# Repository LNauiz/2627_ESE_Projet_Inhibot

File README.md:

# 2627_ESE_Projet_Inhibot
_Projet réalisé par SERAPHIN Bradley, NAVIZET Léonard et BOISBOURDIN Lucas_

---
## Présentation du projet
Le but du projet est de créer un petit robot autonome capable de récupérer des canettes en fonction de leur couleur, par exemple rouge ou verte, et de déposer ces canettes dans une zone définis à l'avance.

Architecture du projet :

---

## Plan de la présentation
* [Conception du PCB](#conception-du-pcb)
* [Mécanique du robot](#mecanique-du-robot)
* [Code](#code)

---
## Conception du PCB
Pour la conception du PCB, plusieurs composants étaient recommandés :

- [Régulateur de tension 3.3V (BU)](https://github.com/LNauiz/2627_ESE_Projet_Inhibot/blob/main/Datasheet/Regulateur3-3V_buxxsd5wg-e.pdf)
- [Chargeur de batterie (BQ25896RTWR)](https://github.com/LNauiz/2627_ESE_Projet_Inhibot/blob/main/Datasheet/bq25896.pdf)
- [Jauge pour la batterie (BQ27220)](https://github.com/LNauiz/2627_ESE_Projet_Inhibot/blob/main/Datasheet/bq27220.pdf)
- [Driver de moteur (DRV8833PWR)](https://github.com/LNauiz/2627_ESE_Projet_Inhibot/blob/main/Datasheet/DriverMotoreducteur_drv8833.pdf)

En plus de ces composants recommandés nous avons ajouté les composants suivant :
- [STM32G431RBT6](https://github.com/LNauiz/2627_ESE_Projet_Inhibot/blob/main/Datasheet/stm32g431rbt6.pdf)
- [Accéléromètre et Gyroscope (LSM6DSLTR)](https://github.com/LNauiz/2627_ESE_Projet_Inhibot/blob/main/Datasheet/Accelerometre%26Gyroscope_LSM6DSLTR.pdf)

---
## Mécanique du robot
Pour réaliser la partie mécanique il fallait savoir quelle format de canette le robot doit récupérer. Le format choisis est le format "Sleek".

---
## Code

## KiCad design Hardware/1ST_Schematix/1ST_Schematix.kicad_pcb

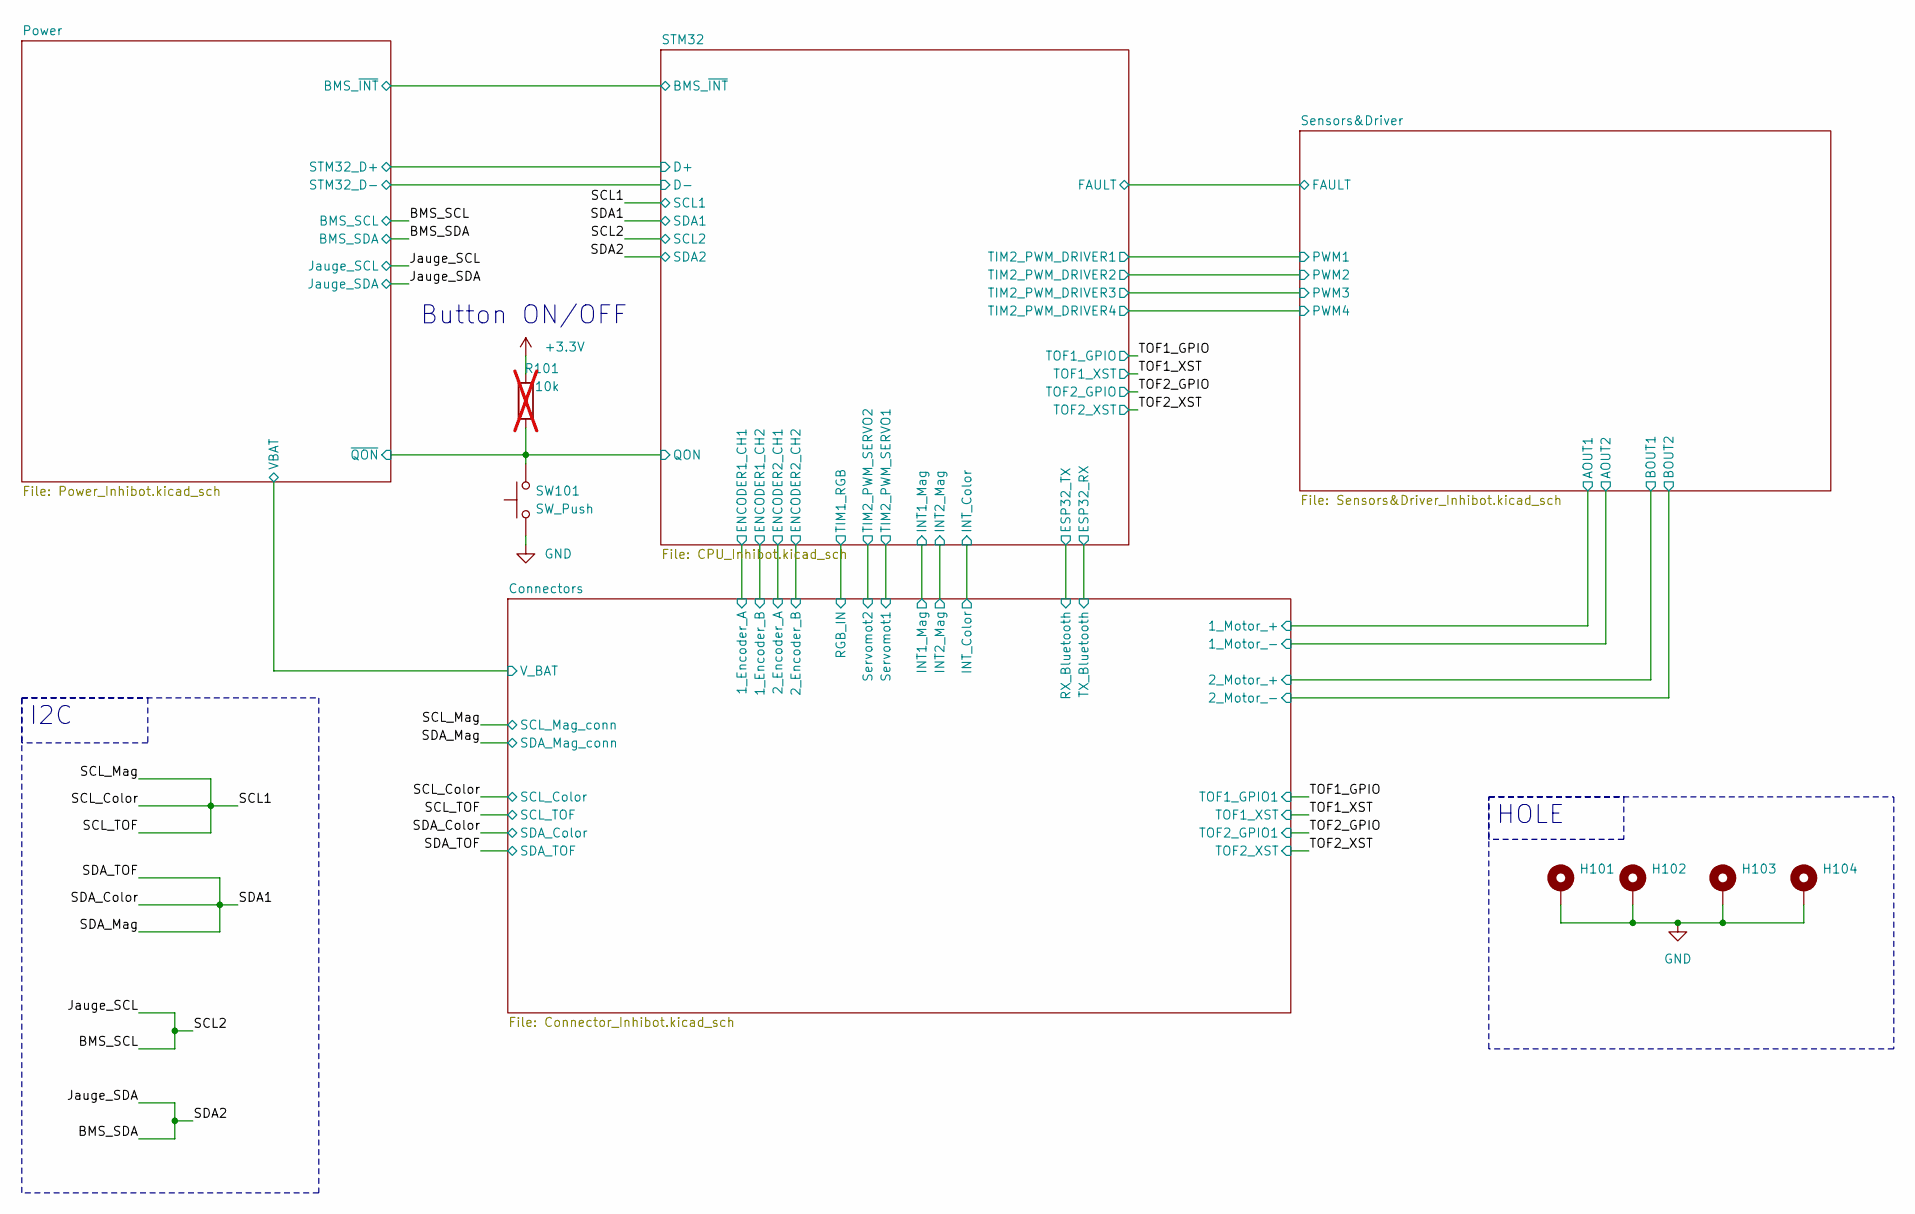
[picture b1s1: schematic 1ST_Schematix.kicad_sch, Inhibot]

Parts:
H101, H102, H103, H104: MountingHole_Pad; MountingHole_3.2mm_M3_ISO14580_Pad
R101: 10k; R_0603_1608Metric_Pad0.98x0.95mm_HandSolder; not fitted
SW101: SW_Push; SW_Push_1P1T_NO_CK_KMR2; JLCPCB Parts # C72443

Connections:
+3.3V: R101.1; also elsewhere on the board
/Power/~QON: R101.2, SW101.2; also elsewhere on the board
GND: H101.1 (1_1), H102.1 (1_1), H103.1 (1_1), H104.1 (1_1), SW101.1; also elsewhere on the board

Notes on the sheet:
Button ON/OFF
I2C
HOLE

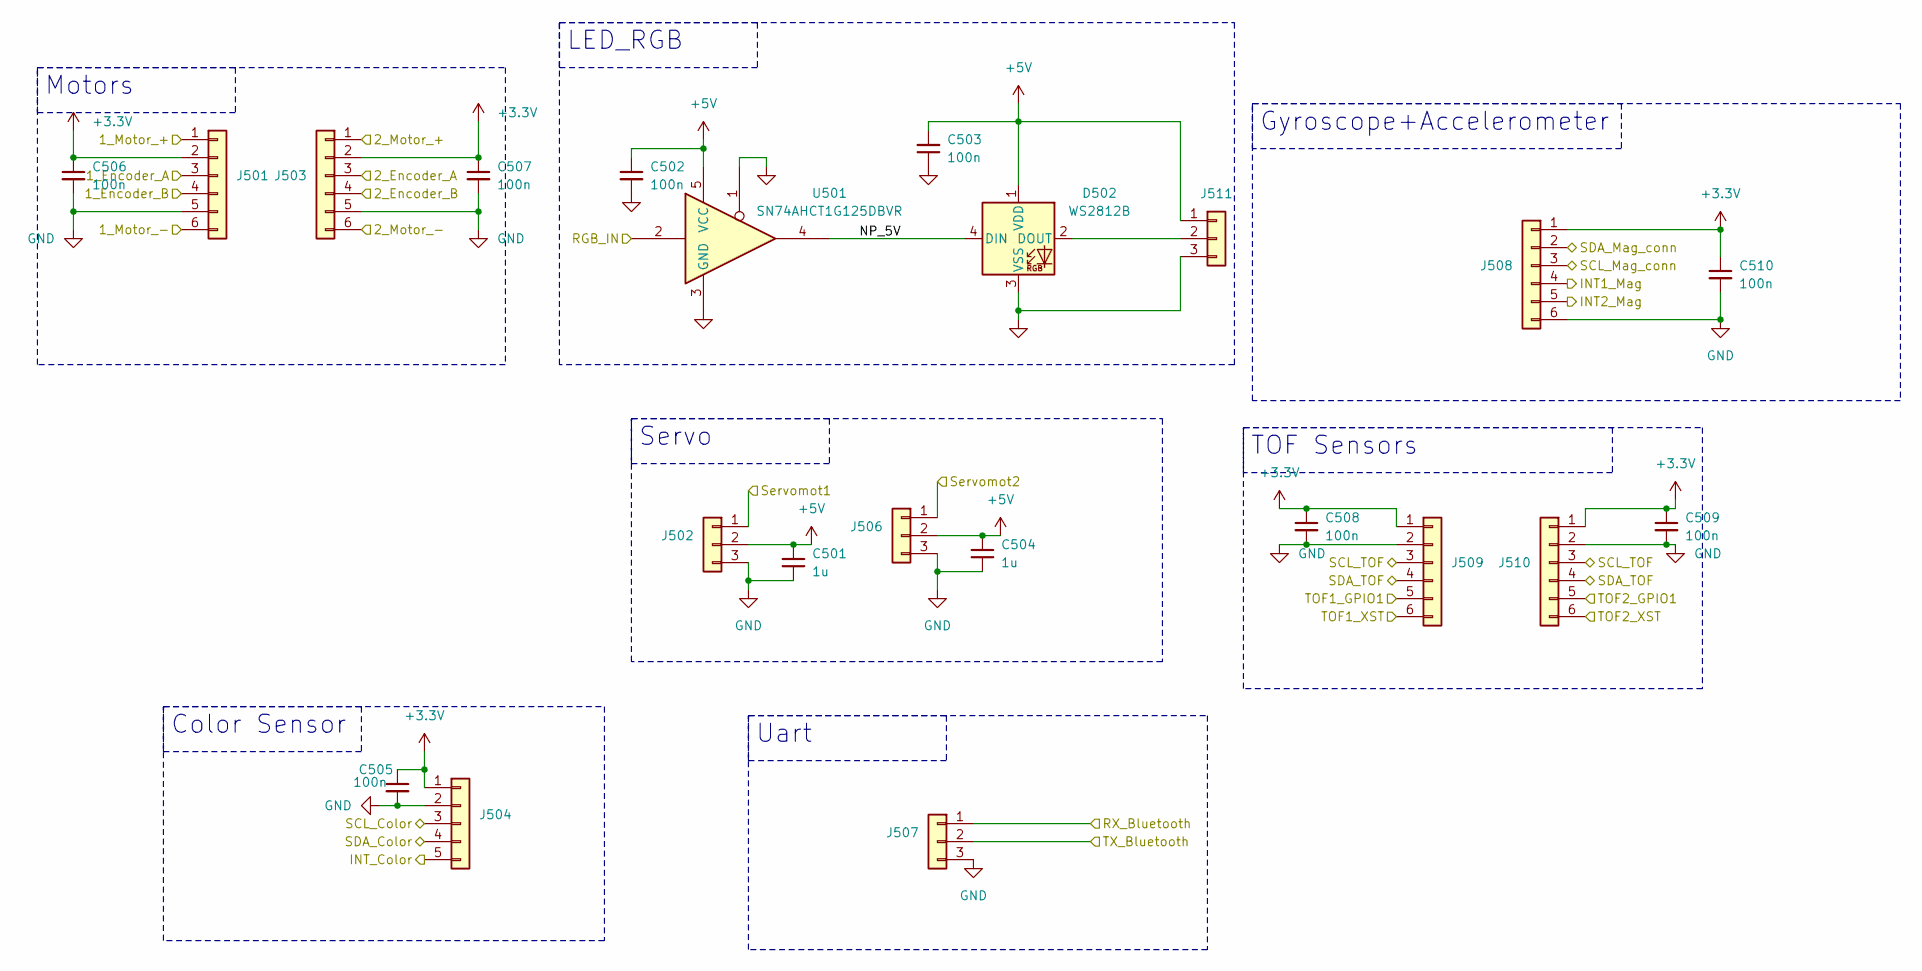
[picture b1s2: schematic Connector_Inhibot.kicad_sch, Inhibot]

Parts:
C501, C504: 1u; C_0402_1005Metric; JLCPCB Parts # C52923
C502, C503, C505, C506, C507, C508, C509, C510: 100n; C_0402_1005Metric; JLCPCB Parts # C1525
D502: WS2812B; LED_WS2812B-Mini_PLCC4_3.5x3.5mm; JLCPCB Parts # C52941386
J501, J503, J508, J509, J510: Conn_01x06; JST_EH_B6B-EH-A_1x06_P2.50mm_Vertical
J502, J506, J507, J511: Conn_01x03; JST_EH_B3B-EH-A_1x03_P2.50mm_Vertical
J504: Conn_01x05; JST_EH_B5B-EH-A_1x05_P2.50mm_Vertical
U501: SN74AHCT1G125DBVR; SOT-23-5; JLCPCB Parts # C20617903

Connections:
+3.3V: C505.1, C506.1, C507.1, C508.1, C509.1, C510.1, J501.2, J503.2, J504.1, J508.1, J509.1, J510.1; also elsewhere on the board
+5V: C501.1, C502.1, C503.2, C504.1, D502.1 (VDD), J502.2, J506.2, J511.1, U501.5 (VCC); also elsewhere on the board
/Connectors/1_Encoder_A: J501.3; also elsewhere on the board
/Connectors/1_Encoder_B: J501.4; also elsewhere on the board
/Connectors/1_Motor_+: J501.1; also elsewhere on the board
/Connectors/1_Motor_-: J501.6; also elsewhere on the board
/Connectors/2_Encoder_A: J503.3; also elsewhere on the board
/Connectors/2_Encoder_B: J503.4; also elsewhere on the board
/Connectors/2_Motor_+: J503.1; also elsewhere on the board
/Connectors/2_Motor_-: J503.6; also elsewhere on the board
/Connectors/INT1_Mag: J508.4; also elsewhere on the board
/Connectors/INT2_Mag: J508.5; also elsewhere on the board
/Connectors/INT_Color: J504.5; also elsewhere on the board
/Connectors/NP_5V: D502.4 (DIN), U501.4
/Connectors/RGB_IN: U501.2; also elsewhere on the board
/Connectors/RX_Bluetooth: J507.1; also elsewhere on the board
/Connectors/Servomot1: J502.1; also elsewhere on the board
/Connectors/Servomot2: J506.1; also elsewhere on the board
/Connectors/TX_Bluetooth: J507.2; also elsewhere on the board
/SCL1: J504.3, J508.3, J509.3, J510.3; also elsewhere on the board
/SDA1: J504.4, J508.2, J509.4, J510.4; also elsewhere on the board
/TOF1_GPIO: J509.5; also elsewhere on the board
/TOF1_XST: J509.6; also elsewhere on the board
/TOF2_GPIO: J510.5; also elsewhere on the board
/TOF2_XST: J510.6; also elsewhere on the board
GND: C501.2, C502.2, C503.1, C504.2, C505.2, C506.2, C507.2, C508.2, C509.2, C510.2, D502.3 (VSS), J501.5, J502.3, J503.5, J504.2, J506.3, J507.3, J508.6, J509.2, J510.2, J511.3, U501.1, U501.3 (GND); also elsewhere on the board
unnamed: D502.2 (DOUT), J511.2

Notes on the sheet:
Uart
LED_RGB
Servo
TOF Sensors
Color Sensor
Gyroscope+Accelerometer
Motors

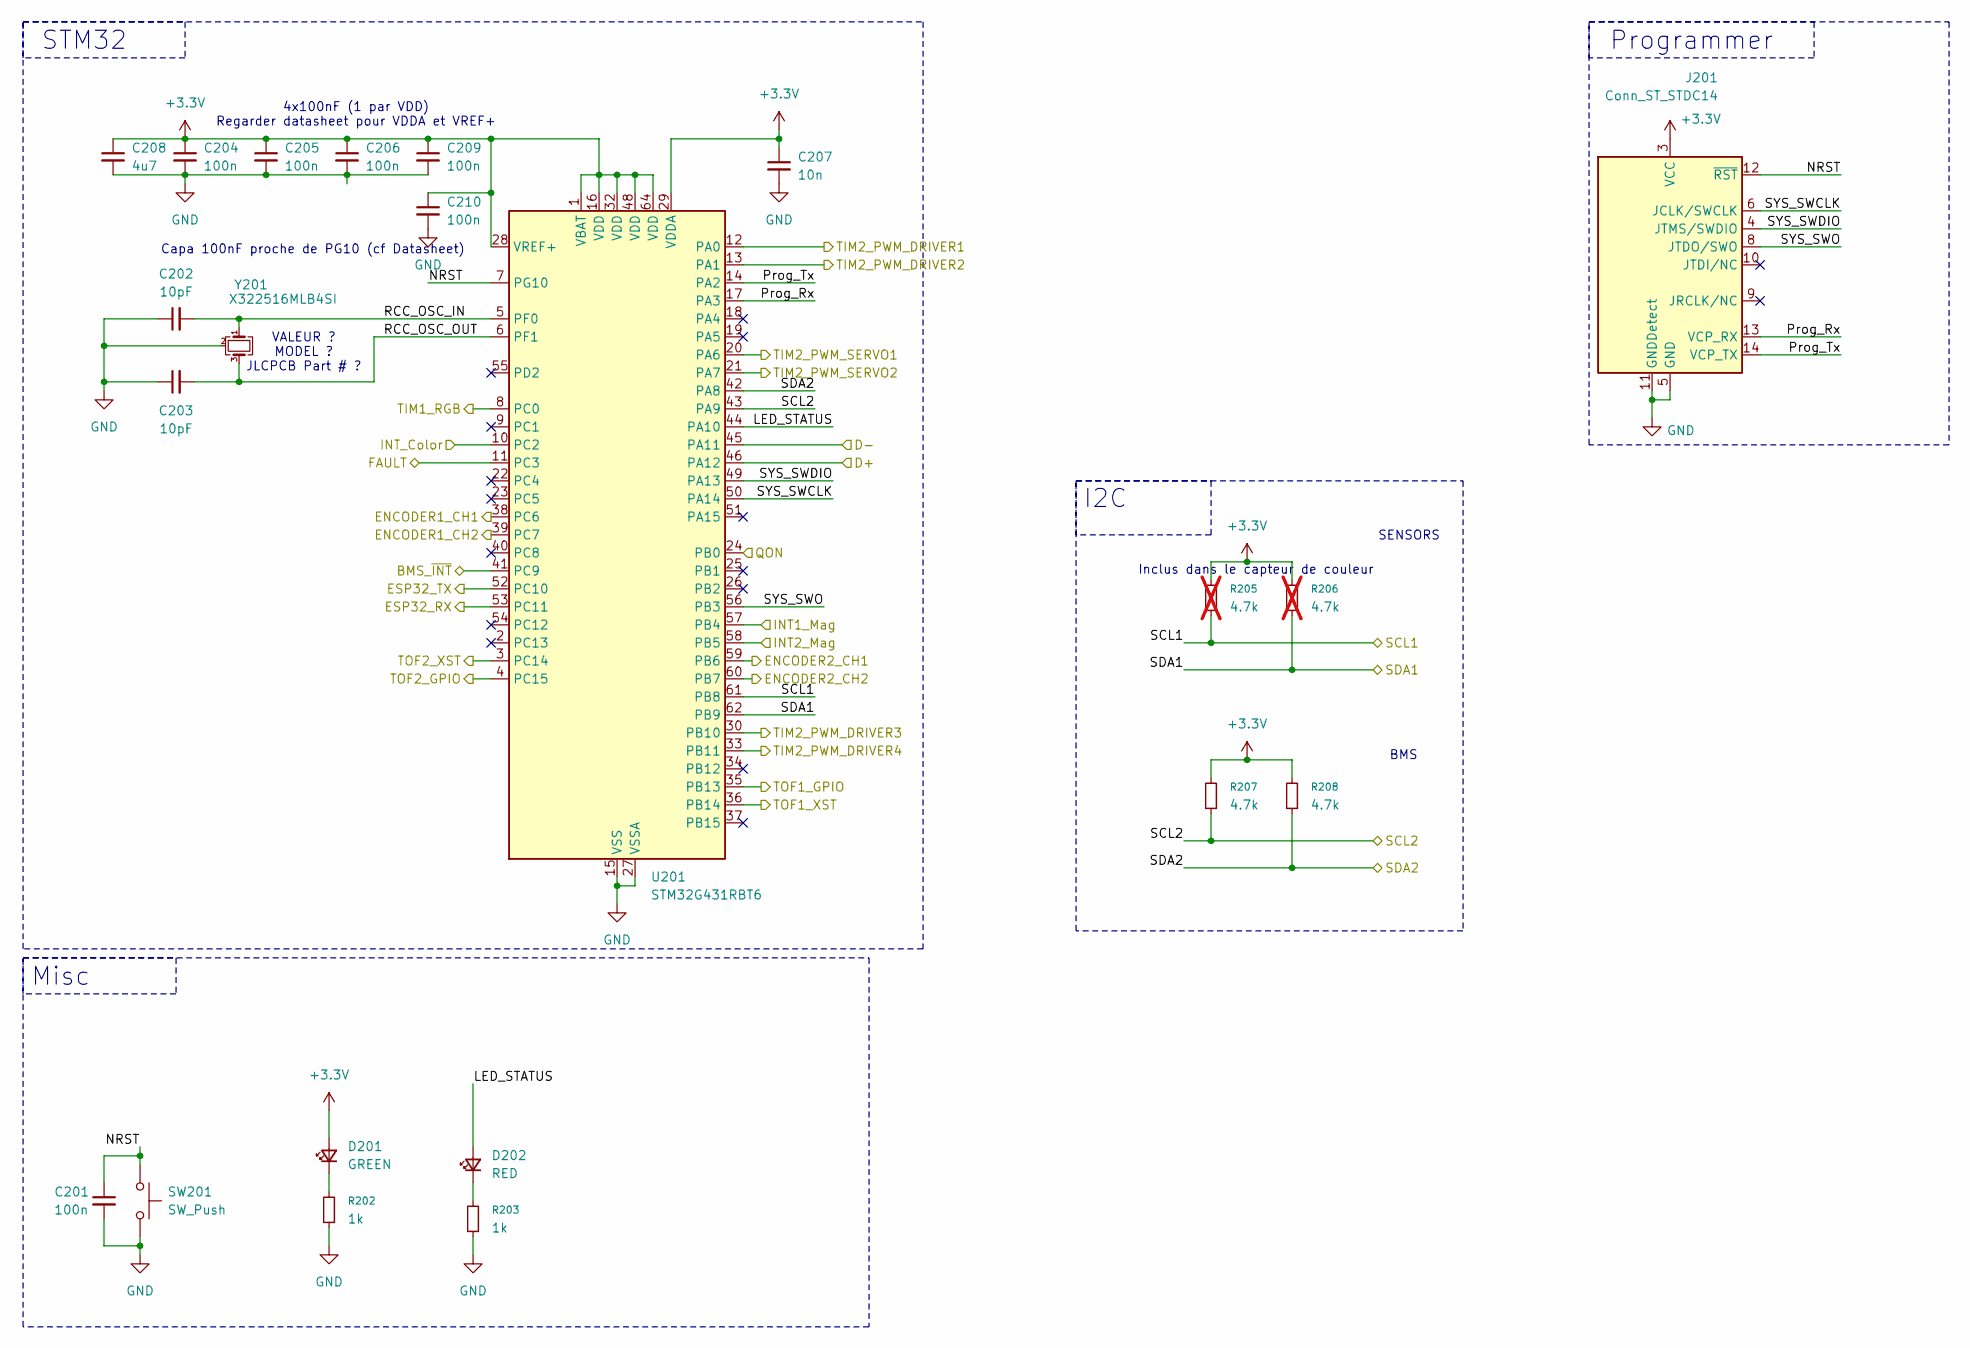
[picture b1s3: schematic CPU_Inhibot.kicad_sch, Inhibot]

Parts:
C201, C204, C205, C206, C209, C210: 100n; C_0402_1005Metric; JLCPCB Parts # C1525
C202, C203: 10pF; C_0402_1005Metric; JLCPCB Parts # C32949
C207: 10n; C_0402_1005Metric; JLCPCB Parts # C15195
C208: 4u7; C_0402_1005Metric; JLCPCB Parts # C23733
D201: GREEN; LED_0603_1608Metric; JLCPCB Parts # C12624
D202: RED; LED_0603_1608Metric; JLCPCB Parts # C2286
J201: Conn_ST_STDC14; PinHeader_2x07_P1.27mm_Vertical_SMD; JLCPCB Parts # C3975190
R202, R203: 1k; R_0402_1005Metric; JLCPCB Parts # C11702
R205, R206: 4.7k; R_0603_1608Metric_Pad0.98x0.95mm_HandSolder; not fitted
R207, R208: 4.7k; R_0402_1005Metric; JLCPCB Parts # C25900
SW201: SW_Push; SW_Push_1P1T_NO_CK_KMR2; MPN KSS221GLFS; JLCPCB Parts # C72443
U201: STM32G431RBT6; LQFP-64_10x10mm_P0.5mm; JLCPCB Parts # C431633
Y201: X322516MLB4SI; Crystal_SMD_EuroQuartz_MT-4Pin_3.2x2.5mm; JLCPCB Parts # C13738

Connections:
+3.3V: C204.1, C205.1, C206.1, C207.1, C208.1, C209.1, C210.1, D201.2 (A), J201.3 (VCC), R205.2, R206.2, R207.2, R208.2, U201.1 (VBAT), U201.16 (VDD), U201.28 (VREF+), U201.29 (VDDA), U201.32 (VDD), U201.48 (VDD), U201.64 (VDD); also elsewhere on the board
/BMS_SCL: R207.1, U201.43 (PA9); also elsewhere on the board
/BMS_SDA: R208.1, U201.42 (PA8); also elsewhere on the board
/Connectors/1_Encoder_A: U201.38 (PC6); also elsewhere on the board
/Connectors/1_Encoder_B: U201.39 (PC7); also elsewhere on the board
/Connectors/2_Encoder_A: U201.59 (PB6); also elsewhere on the board
/Connectors/2_Encoder_B: U201.60 (PB7); also elsewhere on the board
/Connectors/INT1_Mag: U201.57 (PB4); also elsewhere on the board
/Connectors/INT2_Mag: U201.58 (PB5); also elsewhere on the board
/Connectors/INT_Color: U201.10 (PC2); also elsewhere on the board
/Connectors/RGB_IN: U201.8 (PC0); also elsewhere on the board
/Connectors/RX_Bluetooth: U201.52 (PC10); also elsewhere on the board
/Connectors/Servomot1: U201.20 (PA6); also elsewhere on the board
/Connectors/Servomot2: U201.21 (PA7); also elsewhere on the board
/Connectors/TX_Bluetooth: U201.53 (PC11); also elsewhere on the board
/Power/BMS_~INT: U201.41 (PC9); also elsewhere on the board
/Power/STM32_D+: U201.46 (PA12); also elsewhere on the board
/Power/STM32_D-: U201.45 (PA11); also elsewhere on the board
/Power/~QON: U201.24 (PB0); also elsewhere on the board
/SCL1: R205.1, U201.61 (PB8); also elsewhere on the board
/SDA1: R206.1, U201.62 (PB9); also elsewhere on the board
/STM32/FAULT: U201.11 (PC3); also elsewhere on the board
/STM32/LED_STATUS: D202.2 (A), U201.44 (PA10)
/STM32/NRST: C201.1, J201.12 (~RST), SW201.1, U201.7 (PG10)
/STM32/Prog_Rx: J201.13 (VCP_RX), U201.17 (PA3)
/STM32/Prog_Tx: J201.14 (VCP_TX), U201.14 (PA2)
/STM32/RCC_OSC_IN: C202.2, U201.5 (PF0), Y201.1
/STM32/RCC_OSC_OUT: C203.2, U201.6 (PF1), Y201.3
/STM32/SYS_SWCLK: J201.6 (JCLK/SWCLK), U201.50 (PA14)
/STM32/SYS_SWDIO: J201.4 (JTMS/SWDIO), U201.49 (PA13)
/STM32/SYS_SWO: J201.8 (JTDO/SWO), U201.56 (PB3)
/STM32/TIM2_PWM_DRIVER1: U201.12 (PA0); also elsewhere on the board
/STM32/TIM2_PWM_DRIVER2: U201.13 (PA1); also elsewhere on the board
/STM32/TIM2_PWM_DRIVER3: U201.30 (PB10); also elsewhere on the board
/STM32/TIM2_PWM_DRIVER4: U201.33 (PB11); also elsewhere on the board
/TOF1_GPIO: U201.35 (PB13); also elsewhere on the board
/TOF1_XST: U201.36 (PB14); also elsewhere on the board
/TOF2_GPIO: U201.4 (PC15); also elsewhere on the board
/TOF2_XST: U201.3 (PC14); also elsewhere on the board
GND: C201.2, C202.1, C203.1, C204.2, C205.2, C206.2, C207.2, C208.2, C209.2, C210.2, J201.5 (GND), J201.7 (GND), J201.11 (GNDDetect), R202.1, R203.1, SW201.2, U201.15 (VSS), U201.27 (VSSA), U201.31 (VSS), U201.47 (VSS), U201.63 (VSS), Y201.2 (G), Y201.4 (G); also elsewhere on the board
unnamed: D201.1 (K), R202.2
unnamed: D202.1 (K), R203.2

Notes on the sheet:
STM32
Inclus dans le capteur de couleur
4x100nF (1 par VDD) Regarder datasheet pour VDDA et VREF+
SENSORS
Capa 100nF proche de PG10 (cf Datasheet)
BMS
Misc
Programmer
VALEUR ? MODEL ? JLCPCB Part # ?
I2C

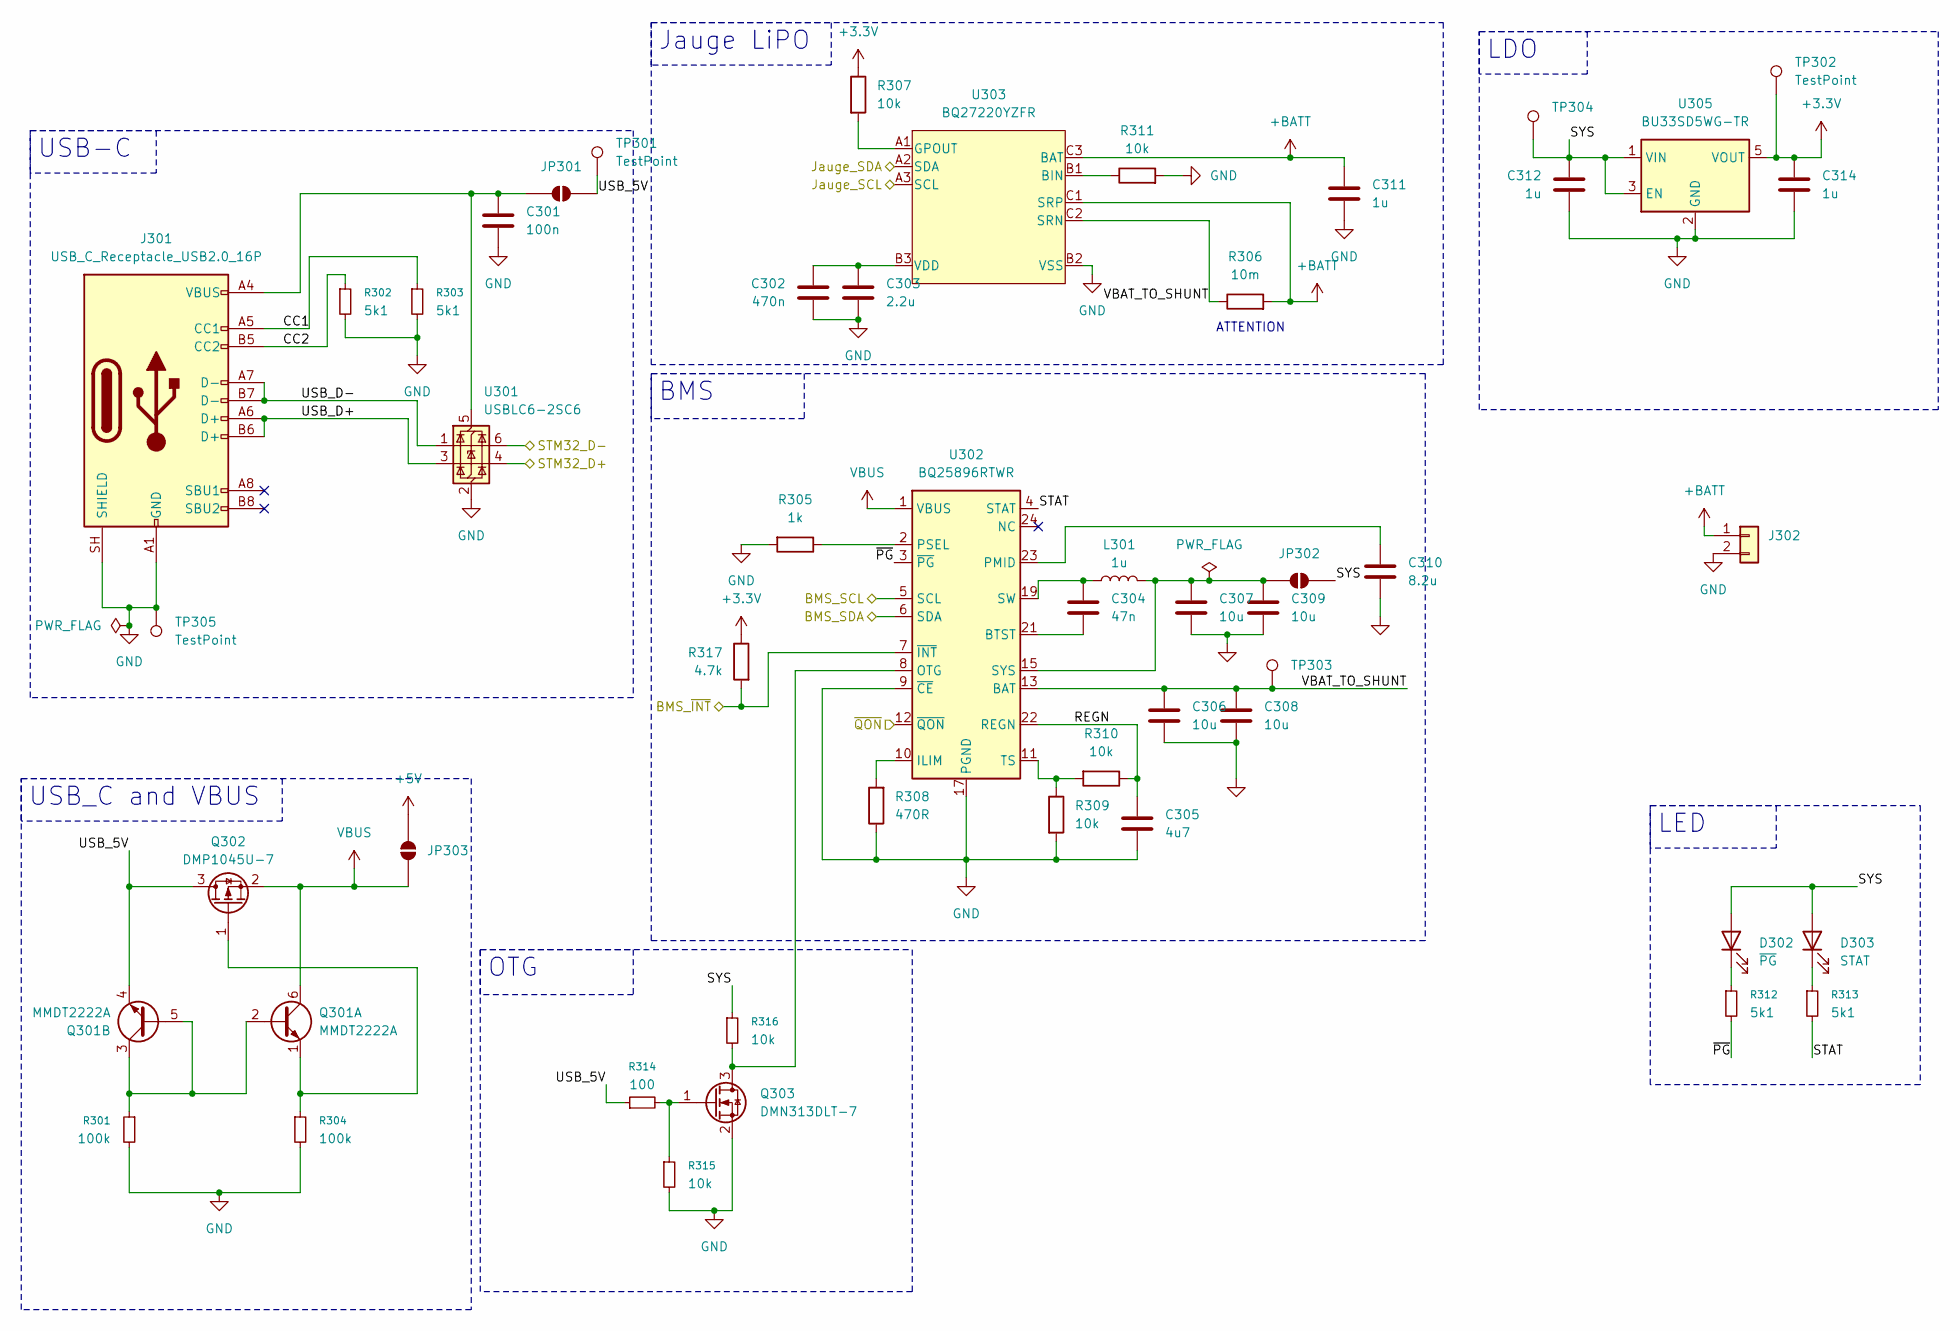
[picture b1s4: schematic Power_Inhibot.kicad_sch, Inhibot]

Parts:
C301: 100n; C_0402_1005Metric; JLCPCB Parts # C1525
C302: 470n; C_0603_1608Metric; JLCPCB Parts # C1623
C303: 2.2u; C_0402_1005Metric; JLCPCB Parts # C12530
C304: 47n; C_0402_1005Metric; JLCPCB Parts # C880605
C305: 4u7; C_0402_1005Metric; JLCPCB Parts # C23733
C306, C307, C308, C309: 10u; C_0402_1005Metric; JLCPCB Parts # C15525
C310: 8.2u; C_1206_3216Metric; JLCPCB Parts # C2182568
C311, C312, C314: 1u; C_0402_1005Metric; JLCPCB Parts # C52923
D302: ~{PG}; LED_0603_1608Metric; JLCPCB Parts # C12624
D303: STAT; LED_0603_1608Metric; JLCPCB Parts # C111340
J301: USB_C_Receptacle_USB2.0_16P; USB_C_Receptacle_GCT_USB4105-xx-A_16P_TopMnt_Horizontal; JLCPCB Parts # C2765186
J302: Conn_01x02; JST_EH_B2B-EH-A_1x02_P2.50mm_Vertical
JP301, JP302, JP303: SolderJumper_2_Open; SolderJumper-2_P1.3mm_Open_TrianglePad1.0x1.5mm
L301: 1u; JLCPCB Parts # C84468
Q301: MMDT2222A; SOT-363_SC-70-6; JLCPCB Parts # C7603394
Q302: DMP1045U-7; SOT-23; JLCPCB Parts # C177033
Q303: DMN313DLT-7; SOT-523; JLCPCB Parts # C155524
R301, R304: 100k; R_0402_1005Metric; JLCPCB Parts # C25741
R302, R303, R312, R313: 5k1; R_0402_1005Metric; JLCPCB Parts # C25905
R305: 1k; R_0402_1005Metric; JLCPCB Parts # C11702
R306: 10m; R_2512_6332Metric; JLCPCB Parts # C105142
R307, R309, R310, R311, R315, R316: 10k; R_0402_1005Metric; JLCPCB Parts # C25744
R308: 470R; R_0402_1005Metric; JLCPCB Parts # C25117
R314: 100; R_0402_1005Metric; JLCPCB Parts # C25076
R317: 4.7k; R_0402_1005Metric; JLCPCB Parts # C25900
TP301, TP302, TP303, TP304, TP305: TestPoint; TestPoint_Pad_D2.0mm
U301: USBLC6-2SC6; SOT-23-6; JLCPCB Parts # C7519
U302: BQ25896RTWR; Texas_RTW_WQFN-24-1EP_4x4mm_P0.5mm_EP2.7x2.7mm; JLCPCB Parts # C181475
U303: BQ27220YZFR; Texas_DSBGA-9_1.4715x1.4715mm_Layout3x3_P0.5mm; JLCPCB Parts # C528617
U305: BU33SD5WG-TR; TSOT-23-5; JLCPCB Parts # C3750265

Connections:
+3.3V: C314.1, R307.1, R317.1, TP302.1 (1_1), U305.5 (VOUT); also elsewhere on the board
+5V: JP303.2 (B); also elsewhere on the board
+BATT: C311.1, J302.1, R306.2, U303.C1 (SRP), U303.C3 (BAT)
/BMS_SCL: U302.5 (SCL), U303.A3 (SCL); also elsewhere on the board
/BMS_SDA: U302.6 (SDA), U303.A2 (SDA); also elsewhere on the board
/Power/BMS_~INT: R317.2, U302.7 (~INT); also elsewhere on the board
/Power/CC1: J301.A5 (CC1), R303.1
/Power/CC2: J301.B5 (CC2), R302.1
/Power/REGN: C305.2, R310.1, U302.22 (REGN)
/Power/STAT: R313.2, U302.4 (STAT)
/Power/STM32_D+: U301.4 (I/O2); also elsewhere on the board
/Power/STM32_D-: U301.6 (I/O1); also elsewhere on the board
/Power/SYS: C312.1, D302.2 (A), D303.2 (A), JP302.2 (B), R316.1, TP304.1 (1_1), U305.1 (VIN), U305.3 (EN)
/Power/USB_5V: JP301.2 (B), Q301.4 (E2), Q302.3 (D), R314.1, TP301.1 (1_1)
/Power/USB_D+: J301.A6 (D+), J301.B6 (D+), U301.3 (I/O2)
/Power/USB_D-: J301.A7 (D-), J301.B7 (D-), U301.1 (I/O1)
/Power/VBAT_TO_SHUNT: C306.1, C308.1, R306.1, TP303.1 (1_1), U302.13 (BAT), U302.14 (BAT), U303.C2 (SRN)
/Power/~PG: R312.2, U302.3 (~PG)
/Power/~QON: U302.12 (~QON); also elsewhere on the board
GND: C301.2, C302.2, C303.2, C305.1, C306.2, C307.2, C308.2, C309.2, C310.2, C311.2, C312.2, C314.2, J301.A1 (GND), J301.A12 (GND), J301.B1 (GND), J301.B12 (GND), J301.SH (SHIELD), J302.2, Q303.2 (S), R301.2, R302.2, R303.2, R304.2, R305.2, R308.1, R309.2, R311.2, R315.2, TP305.1 (1_1), U301.2 (GND), U302.9 (~CE), U302.17 (PGND), U302.18 (PGND), U302.25 (PGND), U303.B2 (VSS), U305.2 (GND); also elsewhere on the board
unnamed: C304.2, L301.1, U302.19 (SW), U302.20 (SW)
unnamed: D302.1 (K), R312.1
unnamed: D303.1 (K), R313.1
unnamed: C301.1, J301.A4 (VBUS), J301.A9 (VBUS), J301.B4 (VBUS), J301.B9 (VBUS), JP301.1 (A), U301.5 (VBUS)
unnamed: C307.1, C309.1, JP302.1 (A), L301.2, U302.15 (SYS), U302.16 (SYS)
unnamed: Q301.2 (B1), Q301.3 (C2), Q301.5 (B2), R301.1
unnamed: Q301.1 (E1), Q302.1 (G), R304.1
unnamed: Q303.3 (D), R316.2, U302.8 (OTG)
unnamed: Q303.1 (G), R314.2, R315.1
unnamed: C304.1, U302.21 (BTST)
unnamed: R308.2, U302.10 (ILIM)
unnamed: C310.1, U302.23 (PMID)
unnamed: R305.1, U302.2 (PSEL)
unnamed: R309.1, R310.2, U302.11 (TS)
unnamed: R311.1, U303.B1 (BIN)
unnamed: R307.2, U303.A1 (GPOUT)
unnamed: C302.1, C303.1, U303.B3 (VDD)
VBUS: JP303.1 (A), Q301.6 (C1), Q302.2 (S), U302.1 (VBUS)

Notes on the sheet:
ATTENTION
LED
OTG
LDO
Jauge LiPO
USB-C
BMS
USB_C and VBUS

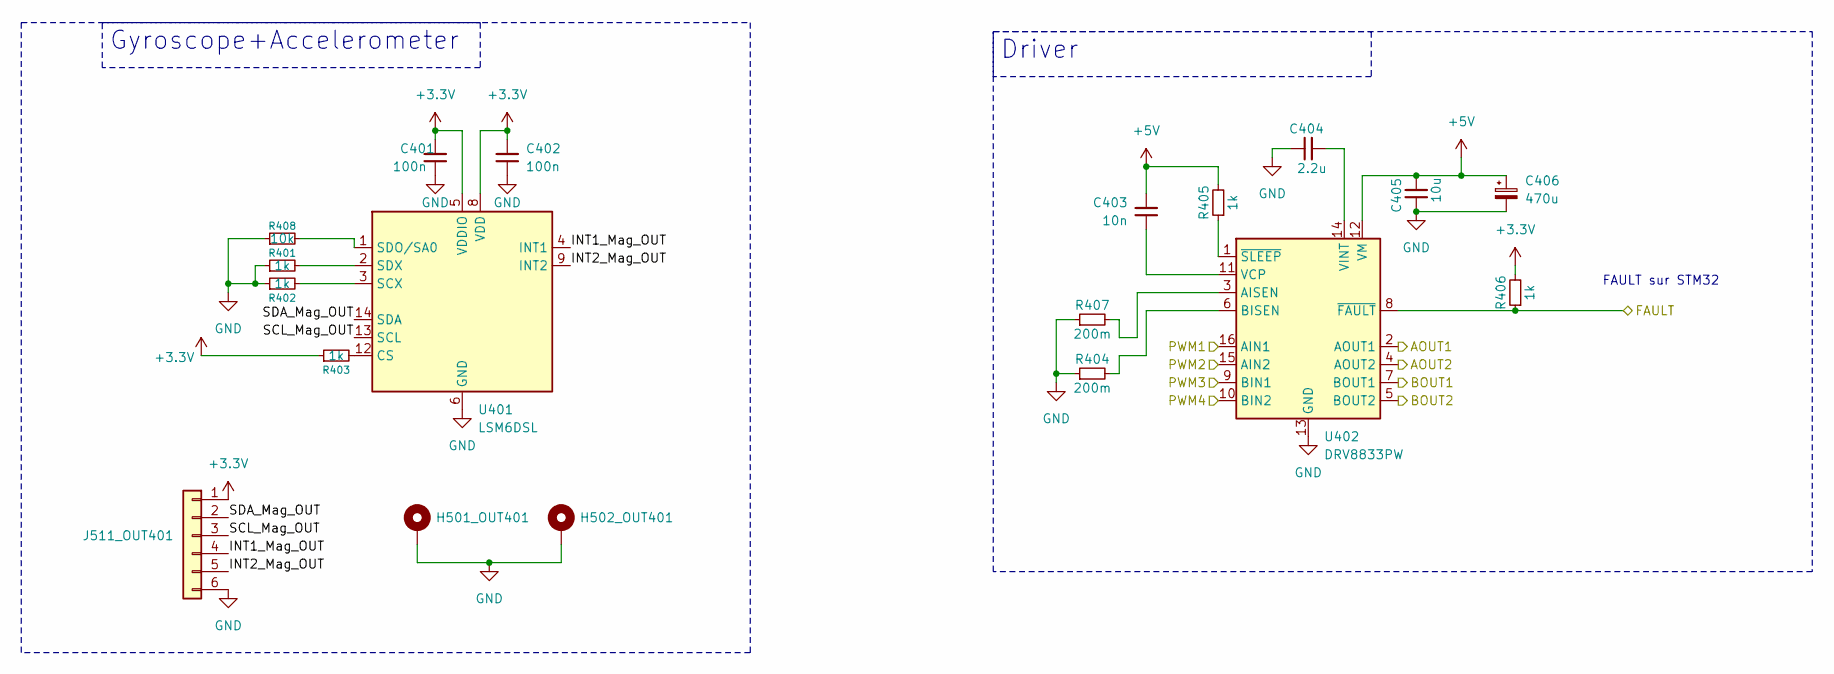
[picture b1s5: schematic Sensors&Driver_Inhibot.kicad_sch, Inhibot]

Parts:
C401, C402: 100n; C_0402_1005Metric; JLCPCB Part # C1525
C403: 10n; C_0402_1005Metric
C404: 2.2u; C_0402_1005Metric
C405: 10u; C_0402_1005Metric
C406: 470u; CP_Elec_10x10.5; JLCPCB Part # C178566
H501_OUT401, H502_OUT401: MountingHole_Pad; MountingHole_3.2mm_M3_ISO14580_Pad
J511_OUT401: Conn_01x06; JST_EH_B6B-EH-A_1x06_P2.50mm_Vertical
R401, R402, R403, R405, R406: 1k; R_0402_1005Metric
R404, R407: 200m; R_0805_2012Metric; JLCPCB Part # C2074761
R408: 10k; R_0402_1005Metric
U401: LSM6DSL; LGA-14_3x2.5mm_P0.5mm_LayoutBorder3x4y; JLCPCB Parts C126672
U402: DRV8833PW; TSSOP-16_4.4x5mm_P0.65mm

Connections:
+3.3V: C401.1, C402.1, J511_OUT401.1, R403.1, R406.2, U401.5 (VDDIO), U401.8 (VDD); also elsewhere on the board
+5V: C403.2, C405.2, C406.1, R405.2, U402.12 (VM); also elsewhere on the board
/Connectors/1_Motor_+: U402.5 (BOUT2); also elsewhere on the board
/Connectors/1_Motor_-: U402.7 (BOUT1); also elsewhere on the board
/Connectors/2_Motor_+: U402.2 (AOUT1); also elsewhere on the board
/Connectors/2_Motor_-: U402.4 (AOUT2); also elsewhere on the board
/STM32/FAULT: R406.1, U402.8 (~FAULT); also elsewhere on the board
/STM32/TIM2_PWM_DRIVER1: U402.16 (AIN1); also elsewhere on the board
/STM32/TIM2_PWM_DRIVER2: U402.15 (AIN2); also elsewhere on the board
/STM32/TIM2_PWM_DRIVER3: U402.10 (BIN2); also elsewhere on the board
/STM32/TIM2_PWM_DRIVER4: U402.9 (BIN1); also elsewhere on the board
/Sensors&Driver/INT1_Mag_OUT: J511_OUT401.4, U401.4 (INT1)
/Sensors&Driver/INT2_Mag_OUT: J511_OUT401.5, U401.9 (INT2)
/Sensors&Driver/SCL_Mag_OUT: J511_OUT401.3, U401.13 (SCL)
/Sensors&Driver/SDA_Mag_OUT: J511_OUT401.2, U401.14 (SDA)
GND: C401.2, C402.2, C404.1, C405.1, C406.2, H501_OUT401.1 (1_1), H502_OUT401.1 (1_1), J511_OUT401.6, R401.1, R402.1, R404.1, R407.1, R408.1, U401.6 (GND), U401.7 (GND), U402.13 (GND); also elsewhere on the board
unnamed: R403.2, U401.12 (CS)
unnamed: R402.2, U401.3 (SCX)
unnamed: R408.2, U401.1 (SDO/SA0)
unnamed: R401.2, U401.2 (SDX)
unnamed: R407.2, U402.3 (AISEN)
unnamed: R404.2, U402.6 (BISEN)
unnamed: C403.1, U402.11 (VCP)
unnamed: C404.2, U402.14 (VINT)
unnamed: R405.1, U402.1 (~SLEEP)

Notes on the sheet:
FAULT sur STM32
Driver
Gyroscope+Accelerometer

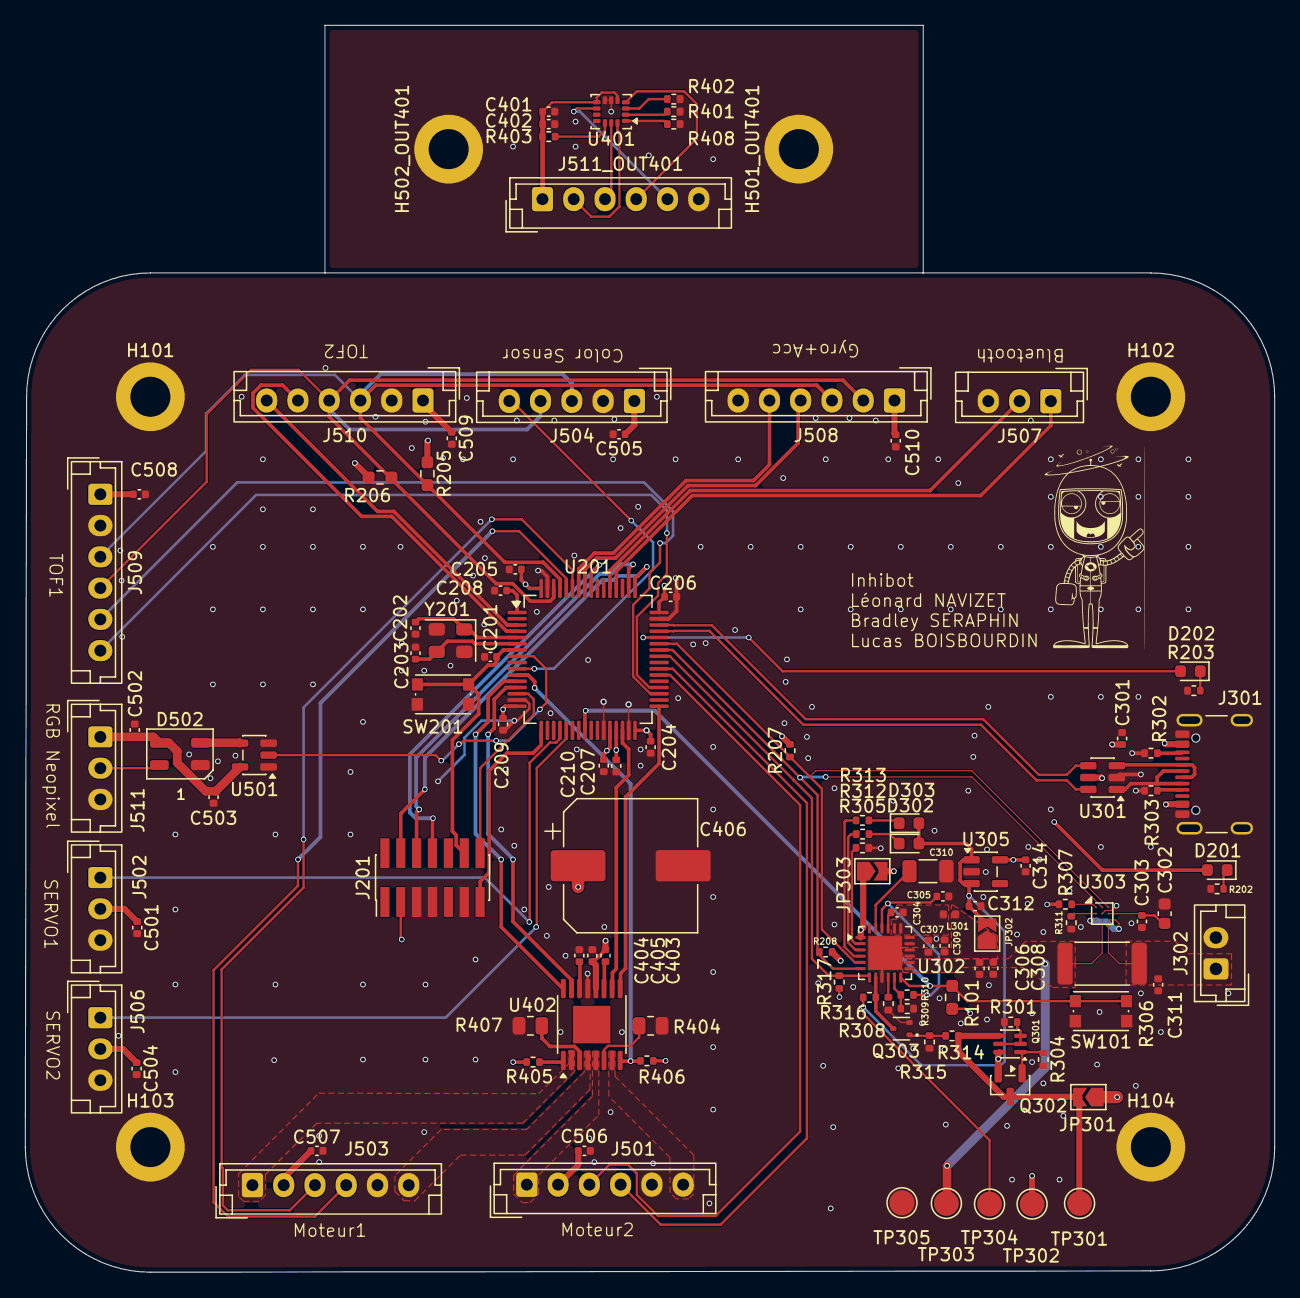
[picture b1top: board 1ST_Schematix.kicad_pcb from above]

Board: 4 copper layers, 99.9 x 79.9 mm, 119 parts (0 on the bottom side), 91 nets.

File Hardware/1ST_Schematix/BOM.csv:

Comment,Designator,Footprint,JLCPCB Part #
10pF,"C202,C203",Capacitor_SMD:C_0402_1005Metric,C32949
10n,"C207,C403",Capacitor_SMD:C_0402_1005Metric,C15195
47n,C304,Capacitor_SMD:C_0402_1005Metric,C880605
100n,"C201,C204,C205,C206,C209,C210,C301,C401,C402,C502,C503,C505,C506,C507,C508,C509,C510",Capacitor_SMD:C_0402_1005Metric,C1525
470n,C302,Capacitor_SMD:C_0603_1608Metric,C1623
1u,"C311,C312,C314,C501,C504",Capacitor_SMD:C_0402_1005Metric,C52923
1u,L301,,C84468
2.2u,"C303,C404",Capacitor_SMD:C_0402_1005Metric,C12530
4u7,"C208,C305",Capacitor_SMD:C_0402_1005Metric,C23733
8.2u,C310,Capacitor_SMD:C_1206_3216Metric,C2182568
10u,"C306,C307,C308,C309,C405",Capacitor_SMD:C_0402_1005Metric,C15525
470u,C406,Capacitor_SMD:CP_Elec_10x10.5,C178566
10m,R306,Resistor_SMD:R_2512_6332Metric,C105142
200m,"R404,R407",Resistor_SMD:R_0805_2012Metric,C2074761
100,R314,Resistor_SMD:R_0402_1005Metric,C25076
470R,R308,Resistor_SMD:R_0402_1005Metric,C25117
1k,"R202,R203,R305,R401,R402,R403,R405,R406",Resistor_SMD:R_0402_1005Metric,C11702
4.7k,"R207,R208,R317",Resistor_SMD:R_0402_1005Metric,C25900
5k1,"R302,R303,R312,R313",Resistor_SMD:R_0402_1005Metric,C25905
10k,"R307,R309,R310,R311,R315,R316,R408",Resistor_SMD:R_0402_1005Metric,C25744
100k,"R301,R304",Resistor_SMD:R_0402_1005Metric,C25741
BQ25896RTWR,U302,Package_DFN_QFN:Texas_RTW_WQFN-24-1EP_4x4mm_P0.5mm_EP2.7x2.7mm,C181475
BQ27220YZFR,U303,Package_BGA:Texas_DSBGA-9_1.4715x1.4715mm_Layout3x3_P0.5mm,C528617
BU33SD5WG-TR,U305,Package_TO_SOT_SMD:TSOT-23-5,C3750265
Conn_ST_STDC14,J201,Connector_PinHeader_1.27mm:PinHeader_2x07_P1.27mm_Vertical_SMD,C3975190
DMN313DLT-7,Q303,Package_TO_SOT_SMD:SOT-523,C155524
DMP1045U-7,Q302,Package_TO_SOT_SMD:SOT-23,C177033
DRV8833PW-PR,U402,Package_SO:TSSOP-16-1EP_4.4x5mm_P0.65mm_EP3x3mm,C50506
GREEN,D201,LED_SMD:LED_0603_1608Metric,C12624
LSM6DSL,U401,Package_LGA:LGA-14_3x2.5mm_P0.5mm_LayoutBorder3x4y,C126672
MMDT2222A,Q301,Package_TO_SOT_SMD:SOT-363_SC-70-6,C7603394
RED,D202,LED_SMD:LED_0603_1608Metric,C2286
SN74AHCT1G125DBVR,U501,Package_TO_SOT_SMD:SOT-23-5,C20617903
STAT,D303,LED_SMD:LED_0603_1608Metric,C111340
STM32G431RBT6,U201,Package_QFP:LQFP-64_10x10mm_P0.5mm,C431633
SW_Push,"SW101,SW201",Button_Switch_SMD:SW_Push_1P1T_NO_CK_KMR2,C72443
USB_C_Receptacle_USB2.0_16P,J301,Connector_USB:USB_C_Receptacle_GCT_USB4105-xx-A_16P_TopMnt_Horizontal,C2765186
USBLC6-2SC6,U301,Package_TO_SOT_SMD:SOT-23-6,C7519
WS2812B,D502,LED_SMD:LED_WS2812B-Mini_PLCC4_3.5x3.5mm,C52941386
X322516MLB4SI,Y201,Crystal:Crystal_SMD_EuroQuartz_MT-4Pin_3.2x2.5mm,C13738
~{PG},D302,LED_SMD:LED_0603_1608Metric,C12624
